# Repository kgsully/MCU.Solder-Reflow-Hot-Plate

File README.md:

# Solder Reflow Hot Plate
 ATMEGA328P-AU Based Solder Reflow Hot Plate Design.

 Please refer to the README docx or PDF found in the documentation folder for further information.
 
 Schematics and drawings may be found within the documentation folder (dimensions are in mm). 
 
 3D design / printing models are located under the 'Enclosure' folder.

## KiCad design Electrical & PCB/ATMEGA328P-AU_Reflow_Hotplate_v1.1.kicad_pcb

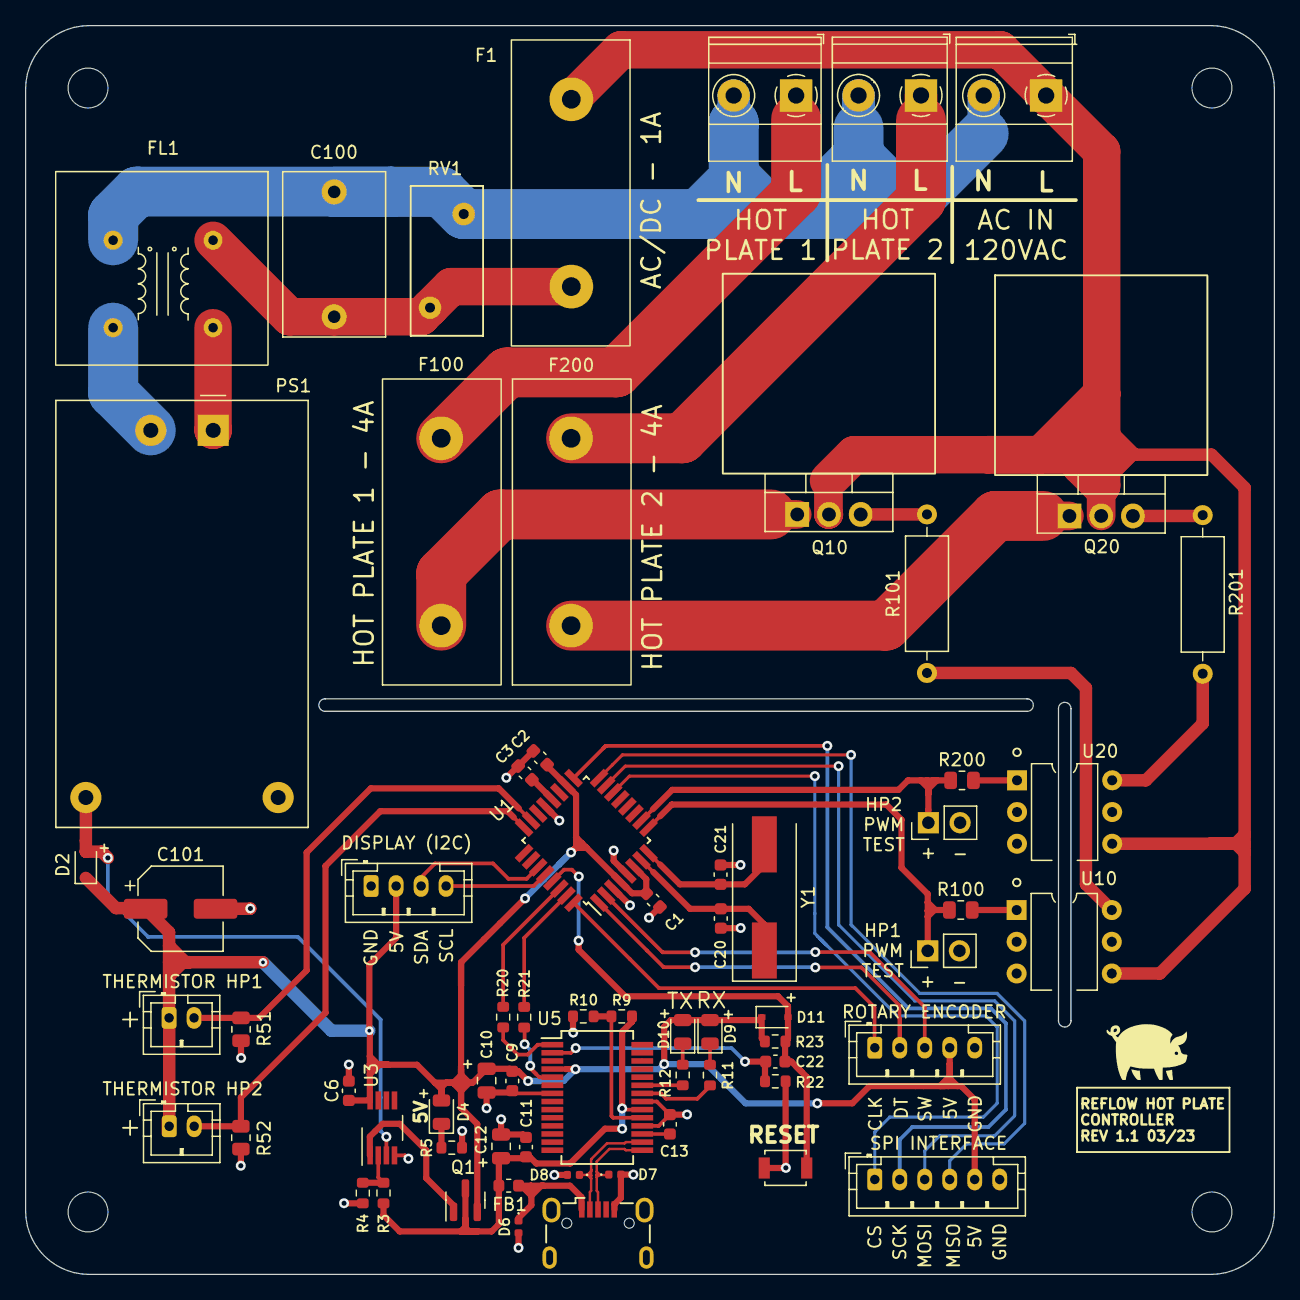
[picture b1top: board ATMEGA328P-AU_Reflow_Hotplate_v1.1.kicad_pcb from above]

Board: 2 copper layers, 100.0 x 100.0 mm, 71 parts (0 on the bottom side), 53 nets.

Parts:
C1, C2, C3, C9, C11, C22: 0.1u; C_0603_1608Metric
C6: 100n; C_0603_1608Metric
C10, C12: 4.7u; C_0805_2012Metric
C13: 1u; C_0603_1608Metric
C20, C21: 22p; C_0603_1608Metric
C100: 0.1uF; C_Rect_L13.0mm_W8.0mm_P10.00mm_FKS3_FKP3_MKS4
C101: 220uF; CP_Elec_6.3x5.9
D2: BAT760,115; D_SOD-323
D4: RED; LED_0805_2012Metric
D6, D7, D8: 5VWM; D_0402_1005Metric
D9, D10: GRN; LED_0805_2012Metric
D11: 1N4148WS; D_SOD-323
F1: 1A; WE 696106003002
F100, F200: 4A; WE 696106003002
FB1: 40R; L_0603_1608Metric
FL1: 14mH; KEMET SU9H-R02140
H1, H2, H3, H4: MountingHole; MountingHole_3.2mm_M3
J3: USB_B_Micro; USB_Micro-B_Wuerth_629105150521
J10, J20: Conn_01x02_Male; JST_PH_B2B-PH-K_1x02_P2.00mm_Vertical
J100, J200, J300: 1935776; TerminalBlock_Phoenix_MKDS-1,5-2_1x02_P5.00mm_Horizontal
J101, J201: Conn_01x02_Male; PinHeader_1x02_P2.54mm_Vertical
J500: Conn_01x04_Male; JST_PH_B4B-PH-K_1x04_P2.00mm_Vertical
J501: Conn_01x05_Male; JST_PH_B5B-PH-K_1x05_P2.00mm_Vertical
J502: Conn_01x06_Male; JST_PH_B6B-PH-K_1x06_P2.00mm_Vertical
PS1: HLK-PM01; Converter_ACDC_HiLink_HLK-PMxx
Q1: DMP2110U-7; SOT-23
Q10, Q20: BT139X-600,127; TO-220-3_Vertical
R3, R4, R10, R23: 10k; R_0603_1608Metric
R5, R11, R12, R20, R21, R22: 1k; R_0603_1608Metric
R9: 4k7; R_0603_1608Metric
R51, R52: 100k; R_0805_2012Metric
R100, R200: 200R; R_0805_2012Metric
R101, R201: 220R; R_Axial_DIN0309_L9.0mm_D3.2mm_P12.70mm_Horizontal
RV1: 10D561K; RV_Disc_D12mm_W5.8mm_P7.5mm
SW1: B3U-1000P; SW_SPST_B3U-1000P
U1: ATmega328P-AU; TQFP-32_7x7mm_P0.8mm
U3: LMV358IDGKR; VSSOP-8_3.0x3.0mm_P0.65mm
U5: CY7C65213-28PVXI; SSOP-28_5.3x10.2mm_P0.65mm
U10, U20: MOC3063M; DIP-6_W7.62mm
Y1: 16MHZ; Crystal_SMD_HC49-SD

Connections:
+5V: C1.1, C2.1, C6.1, C9.2, C10.1, C101.1, D2.1 (K), D4.2 (A), D9.2 (A), D10.2 (A), D11.1 (K), J10.1, J20.1, J500.2, J501.4, J502.5, Q1.2 (S), R23.1, U1.4 (VCC), U1.6 (VCC), U1.18 (AVCC), U3.8 (V+), U5.4 (VCCIO)
/ATMega328P-AU MCU/A0: J10.2, R51.2, U1.23 (A0/PC0)
/ATMega328P-AU MCU/A1: J20.2, R52.2, U1.24 (A1/PC1)
/ATMega328P-AU MCU/A4/SDA: J500.3, U1.27 (A4/PC4)
/ATMega328P-AU MCU/A5/SCL: J500.4, U1.28 (A5/PC5)
/ATMega328P-AU MCU/AREF: C3.1, U1.20 (AREF)
/ATMega328P-AU MCU/DTR: C22.1, R22.1, U5.2 (DTR)
/ATMega328P-AU MCU/IO2: J501.1, U1.32 (INT0/IO2/PD2)
/ATMega328P-AU MCU/IO3: J501.2, U1.1 (~/INT1/IO3/PD3)
/ATMega328P-AU MCU/IO4: J501.3, U1.2 (IO4/PD4)
/ATMega328P-AU MCU/IO5: J101.1, R100.1, U1.9 (~/IO5/PD5)
/ATMega328P-AU MCU/IO6: J201.1, R200.1, U1.10 (~/IO6/PD6)
/ATMega328P-AU MCU/IO10: J502.1, U1.14 (~/IO10/PB2)
/ATMega328P-AU MCU/IO11/MOSI: J502.3, U1.15 (~/IO11/PB3)
/ATMega328P-AU MCU/IO12/MISO: J502.4, U1.16 (IO12/PB4)
/ATMega328P-AU MCU/IO13/SCK: J502.2, U1.17 (IO13/PB5)
/ATMega328P-AU MCU/RXD/IO0: R20.2, U5.1 (TXD)
/ATMega328P-AU MCU/TXD/IO1: R21.2, U5.5 (RXD)
/Hot Plate Circuits/L1: F1.1, J300.1, Q10.2 (A2), Q20.2 (A2), U10.4, U20.4
/Hot Plate Circuits/N1: C100.2, FL1.1, J100.2, J200.2, J300.2, RV1.1
/Power Supply/VBUS: C11.2, C12.1, FB1.2, Q1.3 (D), R3.1, R9.2, U5.20 (VCC)
/Power Supply/Vps: D2.2 (A), PS1.4 (+Vout), U3.3 (+)
/USB-UART Interface/USB_D+: D7.1 (A1), J3.3 (D+), U5.15 (USBDP)
/USB-UART Interface/USB_D-: D8.1 (A1), J3.2 (D-), U5.16 (USBDM)
GND: C1.2, C2.2, C3.2, C6.2, C9.1, C10.2, C11.1, C12.2, C13.2, C20.1, C21.1, C101.2, D6.2 (A2), D7.2 (A2), D8.2 (A2), J3.5 (GND), J101.2, J201.2, J500.1, J501.5, J502.6, PS1.3 (GND), R4.2, R5.2, R10.1, R22.2, R51.1, R52.1, SW1.2, U1.3 (GND), U1.5 (GND), U1.21 (GND), U3.4 (V-), U5.7 (GND), U5.18 (GND), U5.21 (GND), U10.2, U20.2
unnamed: C13.1, U5.17 (VCCD)
unnamed: C20.2, U1.7 (XTAL1/PB6), Y1.1
unnamed: C21.2, U1.8 (XTAL2/PB7), Y1.2
unnamed: C22.2, D11.2 (A), R23.2, SW1.1, U1.29 (~RESET/PC6)
unnamed: C100.1, F1.2, FL1.2, RV1.2
unnamed: D4.1 (K), R5.1
unnamed: D6.1 (A1), FB1.1, J3.1 (VBUS)
unnamed: D9.1 (K), R11.2
unnamed: D10.1 (K), R12.2
unnamed: F100.1, Q10.1 (A1)
unnamed: F100.2, J100.1
unnamed: F200.1, Q20.1 (A1)
unnamed: F200.2, J200.1
unnamed: FL1.3, PS1.1 (AC/L)
unnamed: FL1.4, PS1.2 (AC/N)
unnamed: Q1.1 (G), U3.1
unnamed: Q10.3 (G), R101.2
unnamed: Q20.3 (G), R201.2
unnamed: R3.2, R4.1, U3.2 (-)
unnamed: R9.1, R10.2, U5.19 (~RESET)
unnamed: R11.1, U5.22 (GPIO1)
unnamed: R12.1, U5.23 (GPIO0)
unnamed: R20.1, U1.30 (IO0/PD0)
unnamed: R21.1, U1.31 (IO1/PD1)
unnamed: R100.2, U10.1
unnamed: R101.1, U10.6
unnamed: R200.2, U20.1
unnamed: R201.1, U20.6

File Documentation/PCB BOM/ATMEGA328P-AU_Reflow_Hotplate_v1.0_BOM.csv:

Id,Designator,Package,Quantity,Designation,Supplier and ref
1,"R10,R4,R3,R23",R_0603_1608Metric,4,10k,
2,"R200,R100",R_0805_2012Metric,2,200R,
3,F1,WE 696106003002,1,1A,
4,"C22,C1,C2,C3,C11,C9",C_0603_1608Metric,6,0.1u,
5,"J10,J20",JST_PH_B2B-PH-K_1x02_P2.00mm_Vertical,2,Conn_01x02_Male,
6,U3,VSSOP-8_3.0x3.0mm_P0.65mm,1,LMV358IDGKR,
7,"D10,D9",LED_0805_2012Metric,2,GRN,
8,"C10,C12",C_0805_2012Metric,2,4.7u,
9,U5,SSOP-28_5.3x10.2mm_P0.65mm,1,CY7C65213-28PVXI,
10,"H4,H2,H1,H3",MountingHole_3.2mm_M3,4,MountingHole,
11,"R101,R201",R_Axial_DIN0309_L9.0mm_D3.2mm_P12.70mm_Horizontal,2,220R,
12,"R11,R22,R5,R12,R21,R20",R_0603_1608Metric,6,1k,
13,C6,C_0603_1608Metric,1,100n,
14,C13,C_0603_1608Metric,1,1u,
15,J502,JST_PH_B6B-PH-K_1x06_P2.00mm_Vertical,1,Conn_01x06_Male,
16,"D8,D7,D6",D_0402_1005Metric,3,5VWM,
17,"F100,F200",WE 696106003002,2,4A,
18,"J100,J200,J300","TerminalBlock_Phoenix_MKDS-1,5-2_1x02_P5.00mm_Horizontal",3,1935776,
19,C100,C_Rect_L13.0mm_W8.0mm_P10.00mm_FKS3_FKP3_MKS4,1,0.1uF,
20,"C21,C20",C_0603_1608Metric,2,22p,
21,J501,JST_PH_B5B-PH-K_1x05_P2.00mm_Vertical,1,Conn_01x05_Male,
22,"U20,U10",DIP-6_W7.62mm,2,MOC3063M,
23,D11,D_SOD-323,1,1N4148WS ,
24,D4,LED_0805_2012Metric,1,RED,
25,FB1,L_0603_1608Metric,1,40-100R,
26,"Q10,Q20",TO-220-3_Vertical,2,"BT139X-600,127",
27,U1,TQFP-32_7x7mm_P0.8mm,1,ATmega328P-AU,
28,RV1,RV_Disc_D12mm_W5.8mm_P7.5mm,1,10D561K,
29,R9,R_0603_1608Metric,1,4k7,
30,"J201,J101",PinHeader_1x02_P2.54mm_Vertical,2,Conn_01x02_Male,
31,"R52,R51",R_0805_2012Metric,2,100k,
32,PS1,Converter_ACDC_HiLink_HLK-PMxx,1,HLK-PM01,
33,FL1,KEMET SU9H-R02140,1,14mH,
34,SW1,SW_SPST_B3U-1000P,1,RESET,
35,J3,USB_Micro-B_Wuerth_629105150521,1,USB_B_Micro,
36,J500,JST_PH_B4B-PH-K_1x04_P2.00mm_Vertical,1,Conn_01x04_Male,
37,Y1,Crystal_SMD_HC49-SD,1,16MHZ,
38,C101,CP_Elec_6.3x5.9,1,220uF,
39,D2,D_SOD-323,1,BAT760-7,
40,Q1,SOT-23,1,DMP2110U-7,

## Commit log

2023-03-26 Update to README
    Update to readme to highlight ground lead attachment to hot plate. It was indicated in assembly drawing but deserved highlighted attention in the readme documentation
2023-05-03 Added library files to electrical / PCB project directory
2025-01-30 Update README.md
    Added pictures to readme
